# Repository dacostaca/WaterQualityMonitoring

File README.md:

# Water Quality Monitoring System 🌊

Un sistema autónomo de monitoreo de calidad del agua basado en ESP32 con cuatro sensores: pH, temperatura, TDS y turbidez. Incluye implementación de Deep Sleep y Watchdog Timer para operación autónoma y monitoreo de errores.

---

## 📋 Tabla de Contenidos

- [Descripción General](#-descripción-general)
- [Estado del Proyecto](#-estado-del-proyecto)
- [Estructura del Repositorio](#-estructura-del-repositorio)
  - [Etapa I - Trabajo Previo](#etapa-i---trabajo-previo)
  - [Etapa II - Desarrollo Actual](#etapa-ii---desarrollo-actual)
  - [Código del Firmware (MonitorAgua_ESP32)](#código-del-firmware-monitoragua_esp32)
  - [Código del Servidor (monitor_agua_pagina)](#código-del-servidor-monitor_agua_pagina)
- [Documentación del Código](#-documentación-del-código)
- [Inicio Rápido](#-inicio-rápido)
- [Requisitos](#-requisitos)
- [Colaboradores](#-colaboradores)
- [Licencia](#-licencia)

---

## 🌟 Descripción General

Este proyecto implementa un sistema de monitoreo de calidad del agua diseñado para operar de forma autónoma. El sistema mide cuatro parámetros críticos del agua (pH, temperatura, TDS y turbidez) y transmite los datos a un servidor web para su visualización y análisis.

### ¿Qué mide el sistema?

- **pH**: Nivel de acidez/alcalinidad del agua (0-14)
- **Temperatura**: Temperatura del agua en °C usando sensor DS18B20
- **TDS (Total Dissolved Solids)**: Concentración de sólidos disueltos en ppm
- **Turbidez**: Claridad del agua en NTU

### Aplicaciones

- Monitoreo ambiental de cuerpos de agua naturales
- Control de calidad en plantas de tratamiento
- Investigación científica y educativa
- Acuicultura y piscicultura
- Sistemas de agua potable

---

## 📌 Estado del Proyecto

**Estado actual**: El desarrollo del proyecto ha sido completado en su Etapa II. El sistema se encuentra funcional y documentado, listo para su uso o para ser retomado por futuros desarrolladores que deseen realizar mejoras o extensiones.

**Última actualización**: 09 de diciembre de 2025 (Etapa II)

---

## 📁 Estructura del Repositorio

```
WaterQualityMonitoring/
│
├── Etapa I/                        # Trabajo previo del proyecto (01-08-2025)
│   ├── diseños_pcb/               # Diseños de PCB originales
│   └── documentacion.pdf          # Documentación de la etapa inicial
│
<<<<<<< HEAD
├── Etapa II/                       # Desarrollo actual (09-12-2025)
=======
├── Etapa II/                       # Desarrollo más reciente 
>>>>>>> 25c87ceb19cd74b694c54b1f2cf4447b98eb3ab7
│   ├── Manual de Usuario.md       # Guía completa para el usuario
│   ├── Pruebas y Validación.pdf   # Documento de pruebas realizadas
│   └── registro sistema de monitoreo.rar  # Fotos y fuente LaTeX
│
├── MonitorAgua_ESP32/             # Código del firmware (ESP32)
│   ├── .vscode/                   # Configuración de Visual Studio Code
│   ├── include/                   # Archivos de cabecera (placeholder)
│   ├── lib/                       # Librerías del proyecto
│   ├── src/                       # Código fuente principal
│   ├── test/                      # Directorio de tests (placeholder)
│   ├── .gitignore                # Archivos ignorados por Git
│   ├── Doxyfile                  # Configuración para Doxygen
│   └── platformio.ini            # Configuración de PlatformIO
│
├── monitor_agua_pagina/           # Código del servidor web
│   ├── web_interface/            # Interfaz web del sistema
│   └── servidor.py               # Servidor Python
│
└── README.md                     # Este archivo
```

---

## 📂 Descripción de Carpetas

### Etapa I - Trabajo Previo

**Fecha de entrega**: 01 de agosto de 2025

La carpeta **`Etapa I/`** contiene el trabajo realizado por los desarrolladores iniciales del proyecto:

#### 📐 Diseños de PCB
- **Ubicación**: `Etapa I/diseños_pcb/`
- **Contenido**: Archivos de diseño de la placa de circuito impreso (PCB) utilizados en las versiones iniciales del proyecto
- **Propósito**: Referencia para entender el hardware original y base para mejoras futuras

#### 📄 Documentación Inicial
- **Ubicación**: `Etapa I/documentacion.pdf`
- **Contenido**: Documentación técnica del proyecto en su fase inicial
- **Incluye**: 
  - Especificaciones originales del sistema
  - Diagramas de conexión
  - Resultados de pruebas preliminares
  - Decisiones de diseño tomadas

**Colaboradores Etapa I:**
- Maria Alejandra González Duque
- Juan Carlos Delgado Figueroa

---

### Etapa II - Desarrollo Actual

**Fecha de entrega**: 09 de diciembre de 2025

La carpeta **`Etapa II/`** contiene el trabajo realizado durante el segundo semestre de 2025:

#### 📖 Manual de Usuario
- **Archivo**: `Etapa II/Manual de Usuario.md`
- **Descripción**: Guía completa y detallada para usuarios finales del sistema
- **Contenido**:
  - Instalación del entorno de desarrollo (Visual Studio Code y PlatformIO)
  - Configuración del hardware y drivers
  - Conexión física de sensores a los pines GPIO
  - Flasheo del programa a la ESP32
  - Configuración de red WiFi
  - Uso del sistema y visualización de datos
  - Solución de problemas comunes
  - Referencias y recursos adicionales
- **Audiencia**: Usuarios finales, técnicos, estudiantes

#### 🧪 Documento de Pruebas y Validación
- **Archivo**: `Etapa II/Pruebas y Validación.pdf`
- **Descripción**: Documentación de todas las pruebas realizadas al sistema
- **Contenido**:
  - Metodología de pruebas
  - Casos de prueba ejecutados
  - Resultados obtenidos
  - Análisis de desempeño del sistema
  - Validación de funcionalidades
  - Conclusiones y recomendaciones
- **Propósito**: Validar el correcto funcionamiento del sistema y documentar su rendimiento

#### 📸 Registro del Sistema (LaTeX)
- **Archivo**: `Etapa II/registro sistema de monitoreo.rar`
- **Contenido**:
  - **Fotografías**: Imágenes del sistema ensamblado, sensores conectados, pruebas en campo
  - **Fuente LaTeX**: Archivos `.tex` del documento de registro
  - **Recursos**: Figuras, tablas y archivos auxiliares para compilar el documento
- **Propósito**: Documentación visual del proyecto y fuente editable para reportes académicos
- **Uso**: Descomprimir el archivo RAR y compilar el documento LaTeX para visualizar el registro completo del sistema

**Colaboradores Etapa II:**
- Daniel Felipe Acosta Castro
- Oscar Santiago Erazo Mora

*Estudiantes de Ingeniería Electrónica, Universidad Nacional de Colombia*

---

### Código del Firmware (MonitorAgua_ESP32)

La carpeta **`MonitorAgua_ESP32/`** contiene todo el código que se ejecuta en la placa ESP32.

#### Estructura del Firmware

```
MonitorAgua_ESP32/
│
├── .vscode/                       # Configuración del entorno VSCode
│   └── [archivos de configuración]
│
├── include/                       # Directorio para archivos de cabecera
│   └── README                    # Archivo placeholder
│
├── lib/                          # Librerías personalizadas del proyecto
│   ├── CalibrationManager/      # Gestión de calibración de sensores
│   │   ├── CalibrationManager.cpp
│   │   └── CalibrationManager.h
│   │
│   ├── DeepSleep/               # Implementación de modo Deep Sleep
│   │   ├── DeepSleep.cpp
│   │   └── DeepSleep.h
│   │
│   ├── RTC/                     # Control del reloj de tiempo real (RTC)
│   │   ├── RTC.cpp
│   │   └── RTC.h
│   │
│   ├── RTCMemory/               # Gestión de memoria del RTC
│   │   ├── RTCMemory.cpp
│   │   └── RTCMemory.h
│   │
│   ├── Sensors/                 # Controladores de sensores
│   │   ├── pH.cpp              # Sensor de pH
│   │   ├── pH.h
│   │   ├── Temperature.cpp     # Sensor de temperatura DS18B20
│   │   ├── Temperature.h
│   │   ├── TDS.cpp             # Sensor TDS
│   │   ├── TDS.h
│   │   ├── Turbidity.cpp       # Sensor de turbidez
│   │   └── Turbidity.h
│   │
│   ├── WatchDog/                # Implementación del Watchdog Timer
│   │   ├── WatchDog.cpp
│   │   └── WatchDog.h
│   │
│   └── WifiManager/             # Gestión de conectividad WiFi
│       ├── WifiManager.cpp
│       └── WifiManager.h
│
├── src/                          # Código fuente principal
│   └── main.cpp                 # Punto de entrada del programa
│
├── test/                         # Directorio para tests unitarios
│   └── README                   # Archivo placeholder
│
├── .gitignore                    # Archivos ignorados por Git
├── Doxyfile                      # Configuración de Doxygen
└── platformio.ini                # Configuración de PlatformIO
```

#### Descripción de Componentes del Firmware

##### Librerías Principales

- **CalibrationManager**: Gestiona los valores de calibración de los sensores, permitiendo ajustar las lecturas para mayor precisión
- **DeepSleep**: Implementa el modo de bajo consumo de energía, haciendo que la ESP32 entre en Deep Sleep entre mediciones para optimizar el uso de batería
- **RTC**: Maneja la comunicación con el módulo de reloj de tiempo real (RTC DS3231) para mantener estampas de tiempo precisas
- **RTCMemory**: Gestiona el almacenamiento de datos en la memoria del RTC que persiste durante los ciclos de Deep Sleep
- **Sensors**: Contiene los controladores para cada uno de los cuatro sensores:
  - **pH**: Sensor analógico de pH que mide acidez/alcalinidad del agua
  - **Temperature**: Sensor digital DS18B20 que usa protocolo OneWire
  - **TDS**: Sensor analógico de sólidos totales disueltos
  - **Turbidity**: Sensor analógico de turbidez que mide claridad del agua
- **WatchDog**: Implementa el temporizador Watchdog para reiniciar automáticamente el sistema en caso de fallos o bloqueos
- **WifiManager**: Gestiona la conexión WiFi, reconexión automática y comunicación con el servidor

##### Código Principal

- **main.cpp**: Programa principal que orquesta todas las funcionalidades:
  - Inicialización de sensores y periféricos
  - Bucle principal de medición
  - Almacenamiento local de datos
  - Gestión de ciclos de Deep Sleep
  - Conexión periódica a WiFi para transmisión de datos

#### Archivos de Configuración

- **platformio.ini**: Define la configuración del proyecto para PlatformIO, incluyendo:
  - Placa objetivo (ESP32)
  - Framework (Arduino)
  - Librerías externas requeridas
  - Velocidad de baudios para comunicación serial
  - Flags de compilación

- **Doxyfile**: Configuración para generar documentación automática del código usando Doxygen

#### Funcionalidades Principales del Firmware

- ⚡ **Adquisición de datos**: Lee valores de los cuatro sensores de forma periódica
- 💾 **Almacenamiento local**: Guarda mediciones en memoria del RTC cuando no hay conectividad
- 🌐 **Conectividad WiFi**: Se conecta a red configurada para transmisión de datos al servidor
- ⏰ **RTC externo**: Mantiene estampas de tiempo precisas con batería de respaldo
- 🔋 **Deep Sleep**: Reduce consumo de energía entrando en modo de bajo consumo entre mediciones
- 🛡️ **Watchdog Timer**: Reinicia automáticamente el sistema ante fallos o bloqueos
- 📊 **Calibración**: Sistema de calibración para ajustar lecturas de sensores
- 📡 **Protocolo OneWire**: Comunicación con sensor de temperatura DS18B20

---

### Código del Servidor (monitor_agua_pagina)

La carpeta **`monitor_agua_pagina/`** contiene el servidor web que recibe y visualiza los datos del sistema.

#### Estructura del Servidor

```
monitor_agua_pagina/
│
├── web_interface/                # Interfaz web del sistema
│   ├── css/                     # Hojas de estilo
│   │   └── styles.css          # Estilos de la interfaz
│   │
│   ├── js/                      # JavaScript del cliente
│   │   └── script.js           # Lógica de la interfaz web
│   │
│   └── index.html               # Página principal
│
└── servidor.py                   # Servidor Python
```

#### Descripción de Componentes del Servidor

##### Servidor Backend

- **servidor.py**: Servidor web implementado en Python que maneja:
  - Recepción de datos enviados por la ESP32
  - Procesamiento y validación de mediciones
  - Almacenamiento temporal de datos
  - Servicio de la interfaz web
  - API para consulta de datos históricos

##### Interfaz Web (web_interface/)

- **index.html**: Página principal de la aplicación web que proporciona:
  - Visualización de datos en tiempo real
  - Gráficos de tendencias de mediciones
  - Tabla con historial de datos (últimas 120 mediciones por defecto)
  - Botón para solicitar datos almacenados en la ESP32
  - Indicadores de estado de conexión

- **styles.css**: Hoja de estilos que define:
  - Diseño y apariencia de la interfaz
  - Estilos para gráficos y tablas
  - Diseño responsivo
  - Indicadores visuales de estado

- **script.js**: JavaScript del lado del cliente que maneja:
  - Solicitudes AJAX al servidor
  - Actualización dinámica de la interfaz
  - Generación de gráficos interactivos
  - Procesamiento y visualización de datos recibidos
  - Gestión de eventos de usuario (botones, filtros, etc.)

#### Funcionalidades del Servidor

- 🌐 **API REST**: Endpoints para recibir datos de la ESP32 vía HTTP
- 📊 **Visualización**: Interfaz web para mostrar datos en tiempo real y tendencias
- 💾 **Almacenamiento temporal**: Mantiene datos recientes en memoria para consulta
- 🔄 **Actualización dinámica**: Refresca automáticamente la interfaz con nuevos datos
- 📈 **Gráficos**: Generación de gráficos de series de tiempo para cada sensor
- 🎨 **Interfaz responsiva**: Diseño adaptable a diferentes tamaños de pantalla

#### Tecnologías Utilizadas

- **Backend**: Python (servidor web)
- **Frontend**: HTML5, CSS3, JavaScript
- **Comunicación**: HTTP/REST API
- **Visualización**: JavaScript (librerías de gráficos integradas en script.js)

---

## 📖 Documentación del Código

### Documentación Doxygen del Firmware

El código del firmware en la carpeta **`MonitorAgua_ESP32/`** está completamente documentado utilizando el estándar **Doxygen**. Esto permite generar documentación HTML profesional de forma automática a partir de los comentarios en el código.

#### ¿Qué es Doxygen?

Doxygen es una herramienta que extrae comentarios especialmente formateados del código fuente y genera documentación en varios formatos (HTML, PDF, LaTeX). Es ampliamente utilizado en proyectos de software para mantener la documentación sincronizada con el código.

#### 📚 Generación de la Documentación

##### Prerrequisitos

Antes de generar la documentación, asegúrese de tener Doxygen instalado:

**Windows:**
1. Descargue el instalador desde: https://www.doxygen.nl/download.html
2. Ejecute el instalador y siga las instrucciones

##### Pasos para Generar la Documentación

1. **Abrir una terminal** (Command Prompt o PowerShell) en la carpeta raíz del firmware:
   ```
   cd MonitorAgua_ESP32
   ```

2. **Ejecutar el comando de Doxygen**:
   ```
   doxygen Doxyfile
   ```

3. **Esperar** a que el proceso termine. Verá mensajes en la terminal indicando el progreso de la generación.

4. **Acceder a la documentación generada**:
   - Una vez completado el proceso, se creará una carpeta llamada **`html/`** dentro del proyecto `MonitorAgua_ESP32/`
   - Navegue a la carpeta: `MonitorAgua_ESP32/html/`
   - Abra el archivo **`index.html`** en su navegador web preferido (doble clic sobre el archivo)

##### Contenido de la Documentación

La documentación generada incluye:

- **Índice de archivos**: Listado de todos los archivos del proyecto con su descripción
- **Índice de clases**: Todas las clases definidas con sus métodos y atributos
- **Índice de funciones**: Listado alfabético de todas las funciones del proyecto
- **Diagramas de clases**: Visualización de relaciones entre clases (requiere Graphviz)
- **Diagramas de dependencias**: Muestra qué archivos dependen de otros
- **Gráficos de llamadas**: Ilustra qué funciones llaman a otras funciones
- **Documentación detallada**: Descripción completa de cada función con:
  - Propósito y funcionalidad
  - Parámetros de entrada
  - Valores de retorno
  - Notas y advertencias
  - Ejemplos de uso (cuando aplica)

##### Navegación de la Documentación

Una vez abierto `index.html`:

1. Use el menú superior para navegar entre secciones:
   - **Files**: Ver todos los archivos del proyecto
   - **Classes**: Ver las clases definidas
   - **Functions**: Buscar funciones específicas

2. Use la barra de búsqueda en la esquina superior derecha para encontrar elementos específicos

3. Haga clic en cualquier elemento para ver su documentación detallada

---

## 🚀 Inicio Rápido

### 1. Clonar el Repositorio

```bash
git clone https://github.com/dacostaca/WaterQualityMonitoring.git
cd WaterQualityMonitoring
```

### 2. Configurar el Firmware (ESP32)

1. Abra Visual Studio Code
2. Instale la extensión PlatformIO IDE
3. Abra la carpeta `MonitorAgua_ESP32` con PlatformIO
4. Conecte la ESP32 al computador mediante USB
5. Compile y flashee el programa usando el botón "Upload" (→) en la barra inferior de PlatformIO

**Nota importante**: El puerto USB Tipo C de la ESP32 solo funciona en **una orientación**. Si el computador no detecta la placa, desconecte el cable USB, voltéelo e intente conectar nuevamente.

### 3. Configurar el Servidor

1. Navegue a la carpeta del servidor:
   ```bash
   cd monitor_agua_pagina
   ```

2. Asegúrese de tener Python instalado en su sistema

3. Ejecute el servidor:
   ```bash
   python servidor.py
   ```

### 4. Acceder a la Interfaz Web

1. Abra su navegador web
2. Vaya a la dirección proporcionada por el servidor (típicamente `http://localhost:5000` o similar)
3. Espere a que la ESP32 se conecte a la red WiFi configurada
4. Use el botón "Solicitar Datos" para descargar las mediciones almacenadas en la ESP32

### 5. Configurar Red WiFi

El sistema está configurado por defecto para conectarse a:
- **SSID**: `RED_MONITOREO`
- **Contraseña**: `Holamundo6`

Para cambiar estas credenciales, edite el archivo de configuración en el firmware y vuelva a flashear el programa.

---

## 🔧 Requisitos

### Hardware

- **Placa**: ESP32 S2 o compatible
- **Sensores DFRobot**:
  - Sensor de pH (analógico)
  - Sensor de temperatura DS18B20 (digital, protocolo OneWire)
  - Sensor TDS (analógico)
  - Sensor de turbidez (analógico)
- **Módulo RTC**: DS3231 con batería CR2032 de 3.3V
- **Cable**: USB Tipo C
- **Alimentación**: 5V (USB o fuente externa)
- **Computador**: Windows 10/11 con puerto USB disponible

### Software

- **[Visual Studio Code](https://code.visualstudio.com/)** - Editor de código
- **[PlatformIO IDE](https://platformio.org/)** - Extensión para VSCode
- **[Python](https://www.python.org/downloads/)** - Para ejecutar el servidor (versión 3.7 o superior)
- **[CP210x USB to UART Bridge Drivers](https://www.silabs.com/developers/usb-to-uart-bridge-vcp-drivers)** - Drivers para comunicación con ESP32
- **[Doxygen](https://www.doxygen.nl/download.html)** - (Opcional) Para generar documentación del código
- **[Graphviz](https://graphviz.org/download/)** - (Opcional) Para diagramas en Doxygen

### Conocimientos Recomendados

- Manejo básico de Visual Studio Code
- Conceptos básicos de electrónica (voltaje, corriente, conexión de sensores)
- Navegación en interfaces web
- Conocimientos básicos de línea de comandos (para ejecutar el servidor)

---

## 📄 Documentación Adicional

Para información detallada sobre el uso del sistema, consulte:

- **[Manual de Usuario](Etapa%20II/Manual%20de%20Usuario.md)**: Guía completa de instalación, configuración y uso
- **[Pruebas y Validación](Etapa%20II/Pruebas%20y%20Validación.pdf)**: Resultados de las pruebas realizadas al sistema
- **[Registro LaTeX](Etapa%20II/registro%20sistema%20de%20monitoreo.rar)**: Documentación visual y fuente LaTeX (descomprimir para acceder)
- **[Documentación Etapa I](Etapa%20I/documentacion.pdf)**: Trabajo previo del proyecto
- **Documentación del código**: Generar con Doxygen siguiendo las instrucciones de la sección anterior

---

## 👥 Colaboradores

### Etapa I (01 de agosto de 2025)
- **Maria Alejandra González Duque**
- **Juan Carlos Delgado Figueroa**

*Responsables del diseño inicial de hardware y primera implementación del sistema*

### Etapa II (09 de diciembre de 2025)
- **Daniel Felipe Acosta Castro** - [GitHub](https://github.com/dacostaca)
- **Oscar Santiago Erazo Mora**

*Estudiantes de Ingeniería Electrónica*  
*Universidad Nacional de Colombia*  
*Segundo semestre de 2025*

---

## 🙏 Agradecimientos

- DFRobot por la documentación de los sensores utilizados
- Comunidad de PlatformIO por las herramientas de desarrollo
- Espressif por el soporte de ESP32
- Universidad Nacional de Colombia por el apoyo académico

---

**⭐ Si este proyecto te fue útil, considera darle una estrella en GitHub ⭐**

---

<<<<<<< HEAD
*Proyecto desarrollado como parte del programa de Ingeniería Electrónica*  
*Universidad Nacional de Colombia - 2025*
=======
*Última actualización: Diciembre 2024*
>>>>>>> 25c87ceb19cd74b694c54b1f2cf4447b98eb3ab7

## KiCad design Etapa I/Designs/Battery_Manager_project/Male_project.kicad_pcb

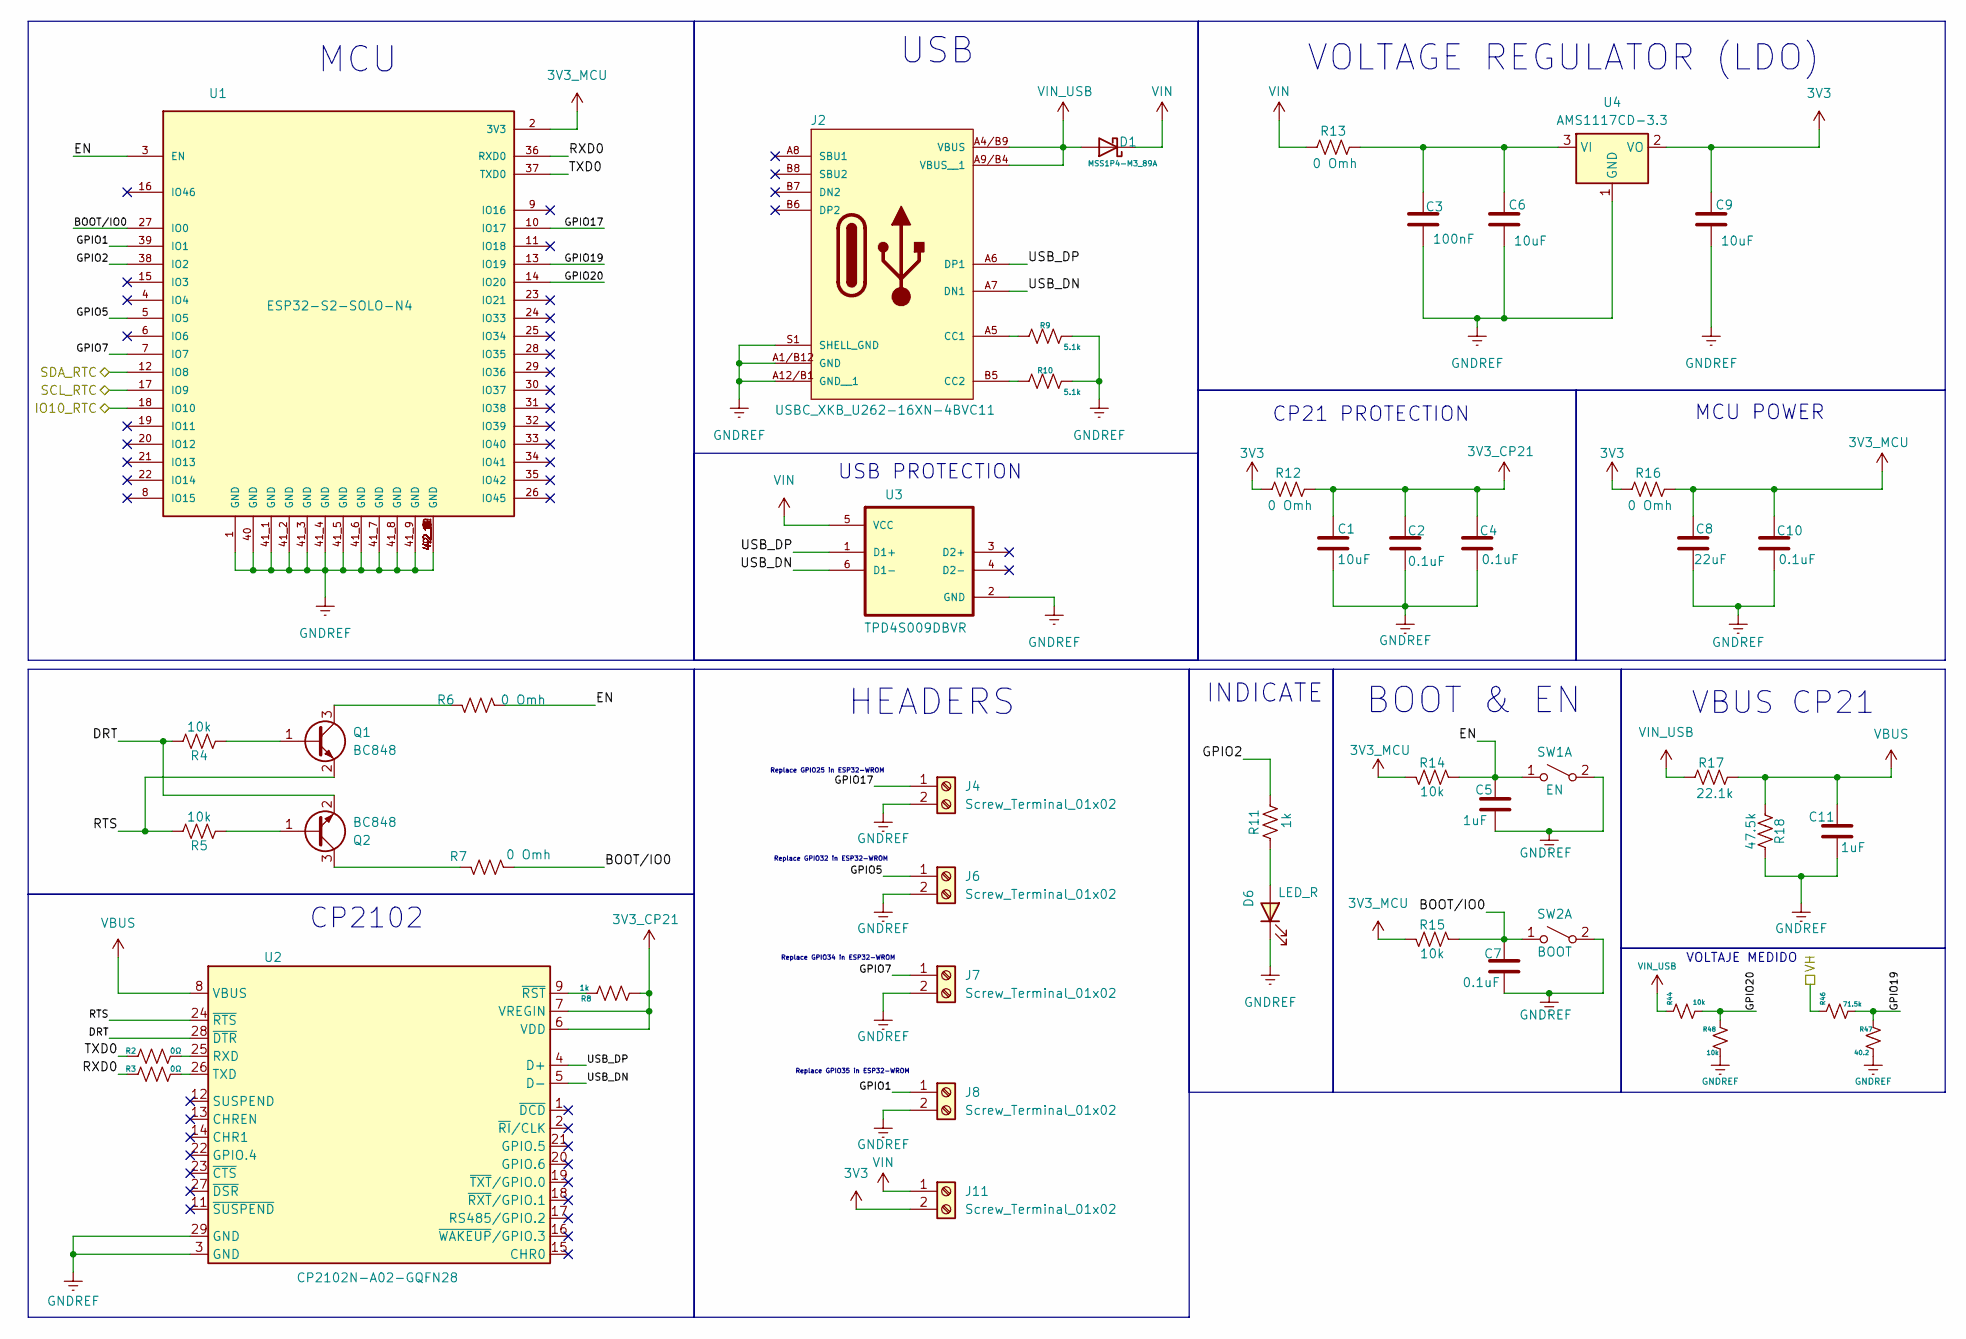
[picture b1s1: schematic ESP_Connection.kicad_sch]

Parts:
C1, C6, C9: 10uF; C_0805_2012Metric
C2, C4, C7, C10: 0.1uF; C_1206_3216Metric
C3: 100nF; C_0603_1608Metric; Mnf. Part # CC0603KRX7R7BB104
C5, C11: 1uF; C_0805_2012Metric; Manufacturer # CC0805KKX7R7BB105
C8: 22uF; C_0805_2012Metric
D1: MSS1P4-M3_89A; DIODE_MSS1P4-M3_89A
D6: LED_R; D_0603_1608Metric; Manufacturer # TLMS1100-GS08
J2: USBC_XKB_U262-16XN-4BVC11; USBC_Receptacle_XKB_U262-16XN-4BVC11; PARTREV B4
J4, J6, J7, J8, J11: Screw_Terminal_01x02; TerminalBlock_MaiXu_MX126-5.0-02P_1x02_P5.00mm
Q1, Q2: BC848; SOT-23
R2, R3: 0Ω; R_0603_1608Metric
R4, R5, R14, R15: 10k; R_0603_1608Metric; Manufacturer # CR0603-FX-1002ELF
R6, R7, R12, R13, R16: 0 Omh; R_0603_1608Metric
R8, R11: 1k; R_0603_1608Metric
R9, R10: 5.1k; R_1206_3216Metric
R17: 22.1k; R_0402_1005Metric
R18: 47.5k; R_0603_1608Metric; Manufacturer # CR0603-FX-1002ELF
R44, R48: 10k; R_0603_1608Metric
R46: 71.5k; R_0603_1608Metric
R47: 40.2; R_0603_1608Metric
SW1: EN; PTS810SJG250SMTR LFS; Manufacturer # PTS810SJG250SMTR LFS
SW2: BOOT; PTS810SJG250SMTR LFS; Manufacturer # PTS810SJG250SMTR LFS
U1: ESP32-S2-SOLO-N4; XCVR_ESP32-S2-SOLO-N4; PARTREV 1.6
U2: CP2102N-A02-GQFN28; QFN-28-1EP_5x5mm_P0.5mm_EP3.35x3.35mm
U3: TPD4S009DBVR; SOT95P280X145-6N
U4: AMS1117CD-3.3; TO-252-2

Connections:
3V3: C9.1, J11.2, R12.1, R16.1, U4.2 (VO); also elsewhere on the board
3V3_CP21: C1.1, C2.1, C4.1, R8.1, R12.2, U2.6 (VDD), U2.7 (VREGIN)
3V3_MCU: C8.1, C10.1, R14.2, R15.2, R16.2, U1.2 (3V3)
/Battery_Manager/IO10_RTC: U1.18 (IO10); also elsewhere on the board
/Battery_Manager/SCL_RTC: U1.17 (IO9); also elsewhere on the board
/Battery_Manager/SDA_RTC: U1.12 (IO8); also elsewhere on the board
/Battery_Manager/VH: R46.1; also elsewhere on the board
/MCU/BOOT/IO0: C7.1, R7.1, R15.1, SW2.1 (B), U1.27 (IO0)
/MCU/DRT: Q2.2 (E), R4.2, U2.28 (~DTR)
/MCU/EN: C5.1, R6.1, R14.1, SW1.1 (B), U1.3 (EN)
/MCU/GPIO1: J8.1, U1.39 (IO1)
/MCU/GPIO2: R11.2, U1.38 (IO2)
/MCU/GPIO5: J6.1, U1.5 (IO5)
/MCU/GPIO7: J7.1, U1.7 (IO7)
/MCU/GPIO17: J4.1, U1.10 (IO17)
/MCU/GPIO19: R46.2, R47.1, U1.13 (IO19)
/MCU/GPIO20: R44.2, R48.1, U1.14 (IO20)
/MCU/RTS: Q1.2 (E), R5.2, U2.24 (~RTS)
/MCU/RXD0: R3.1, U1.36 (RXD0)
/MCU/TXD0: R2.1, U1.37 (TXD0)
/MCU/USB_DN: J2.A7 (DN1), U2.5 (D-), U3.6 (D1-)
/MCU/USB_DP: J2.A6 (DP1), U2.4 (D+), U3.1 (D1+)
GNDREF: C1.2, C2.2, C3.2, C4.2, C5.2, C6.2, C7.2, C8.2, C9.2, C10.2, C11.2, D6.1 (K), J2.A1/B12 (GND), J2.A12/B1 (GND__1), J2.S1 (SHELL_GND), J4.2, J6.2, J7.2, J8.2, R9.2, R10.2, R18.2, R47.2, R48.2, SW1.2 (A), SW2.2 (A), U1.1 (GND), U1.40 (GND), U1.41_1 (GND), U1.41_2 (GND), U1.41_3 (GND), U1.41_4 (GND), U1.41_5 (GND), U1.41_6 (GND), U1.41_7 (GND), U1.41_8 (GND), U1.41_9 (GND), U1.42_1 (GND), U1.42_2 (GND), U1.42_3 (GND), U1.42_4 (GND), U1.42_5 (GND), U1.42_6 (GND), U1.42_7 (GND), U1.42_8 (GND), U1.42_9 (GND), U1.42_10 (GND), U1.42_11 (GND), U1.42_12 (GND), U2.3 (GND), U2.29 (GND), U3.2 (GND), U4.1 (GND); also elsewhere on the board
unnamed: D6.2 (A), R11.1
unnamed: J2.A5 (CC1), R9.1
unnamed: J2.B5 (CC2), R10.1
unnamed: Q1.1 (B), R4.1
unnamed: Q1.3 (C), R6.2
unnamed: Q2.1 (B), R5.1
unnamed: Q2.3 (C), R7.2
unnamed: R2.2, U2.25 (RXD)
unnamed: R3.2, U2.26 (TXD)
unnamed: R8.2, U2.9 (~RST)
unnamed: C3.1, C6.1, R13.2, U4.3 (VI)
VBUS: C11.1, R17.2, R18.1, U2.8 (VBUS)
VIN: D1.1 (K), J11.1, R13.1, U3.5 (VCC); also elsewhere on the board
VIN_USB: D1.2 (A), J2.A4/B9 (VBUS), J2.A9/B4 (VBUS__1), R17.1, R44.1; also elsewhere on the board

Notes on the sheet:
Replace GPIO35 in ESP32-WROM
USB
VOLTAJE MEDIDO
HEADERS
VBUS CP21
INDICATE
MCU
Replace GPIO34 in ESP32-WROM
Replace GPIO25 in ESP32-WROM
USB PROTECTION
Replace GPIO32 in ESP32-WROM
MCU POWER
CP21 PROTECTION
BOOT & EN
VOLTAGE REGULATOR (LDO)
CP2102

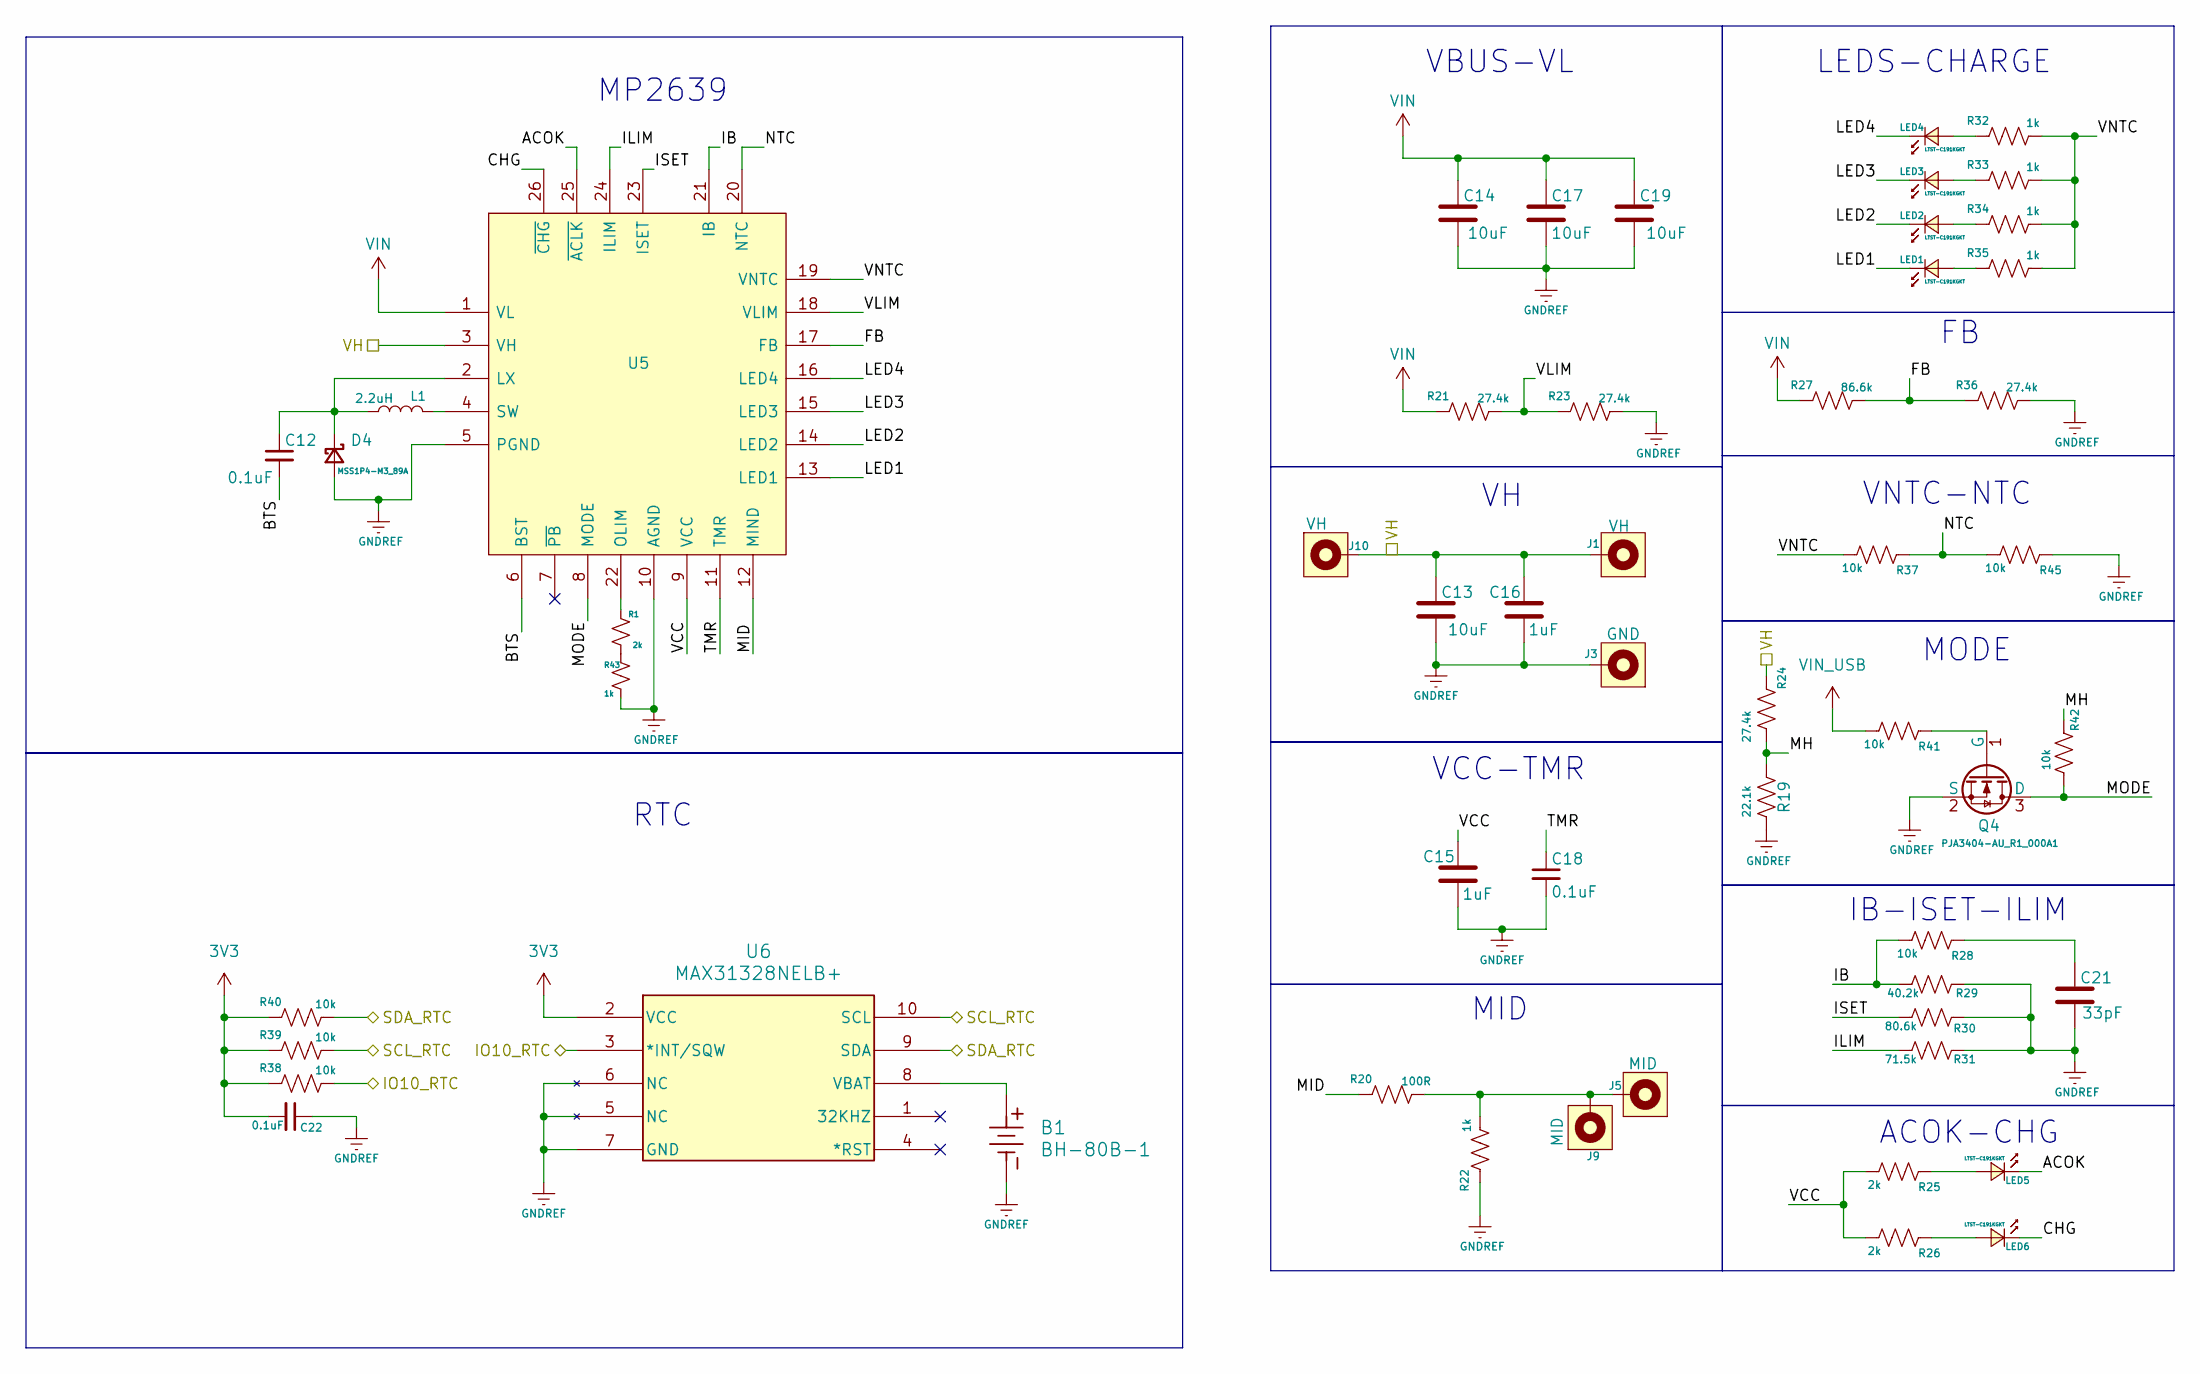
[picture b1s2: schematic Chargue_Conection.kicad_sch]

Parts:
B1: BH-80B-1; BH-80B-1_ADM
C12, C18, C22: 0.1uF; C_0603_1608Metric
C13, C14, C17, C19: 10uF; C_0805_2012Metric
C15, C16: 1uF; C_0805_2012Metric; Manufacturer # CC0805KKX7R7BB105
C21: 33pF; C_0402_1005Metric
D4: MSS1P4-M3_89A; DIODE_MSS1P4-M3_89A
J1, J10: VH; TEST-PIN
J3: GND; TEST-PIN
J5, J9: MID; TEST-PIN
L1: 2.2uH; 0630CDMCCDS-2R2MC___Inductor
LED1, LED2, LED3, LED4, LED5, LED6: LTST-C191KGKT; LED_0603_1608Metric
Q4: PJA3404-AU_R1_000A1; SOT-23
R1, R25, R26: 2k; R_0603_1608Metric
R19: 22.1k; R_0402_1005Metric
R20: 100R; R_0603_1608Metric
R21, R23, R24: 27.4k; C_0603_1608Metric; Man. part# RC0603FR-0727K4L
R22, R32, R33, R34, R35, R43: 1k; R_0603_1608Metric
R27: 86.6k; R_0603_1608Metric
R28, R37, R38, R39, R40, R41, R42, R45: 10k; R_0603_1608Metric
R29: 40.2k; R_0603_1608Metric
R30: 80.6k; R_0603_1608Metric
R31: 71.5k; R_0603_1608Metric
R36: 27.4k; R_0603_1608Metric
U5: MP2639AGR-Z; MP2639AGRZ; Mouser Part Number 946-MP2639AGR-Z
U6: MAX31328NELB+; 21-0140AK_L1055M-1_MXM

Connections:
3V3: C22.2, R38.1, R39.1, R40.1, U6.2 (VCC); also elsewhere on the board
/Battery_Manager/ACOK: LED5.1 (K), U5.25 (~ACLK)
/Battery_Manager/BTS: C12.2, U5.6 (BST)
/Battery_Manager/CHG: LED6.1 (K), U5.26 (~CHG)
/Battery_Manager/FB: R27.2, R36.1, U5.17 (FB)
/Battery_Manager/IB: R28.2, R29.2, U5.21 (IB)
/Battery_Manager/ILIM: R31.2, U5.24 (ILIM)
/Battery_Manager/IO10_RTC: R38.2, U6.3 (*INT/SQW); also elsewhere on the board
/Battery_Manager/ISET: R30.2, U5.23 (ISET)
/Battery_Manager/LED1: LED1.1 (K), U5.13 (LED1)
/Battery_Manager/LED2: LED2.1 (K), U5.14 (LED2)
/Battery_Manager/LED3: LED3.1 (K), U5.15 (LED3)
/Battery_Manager/LED4: LED4.1 (K), U5.16 (LED4)
/Battery_Manager/MH: R19.1, R24.2, R42.1
/Battery_Manager/MID: R20.1, U5.12 (MIND)
/Battery_Manager/MODE: Q4.3 (D), R42.2, U5.8 (MODE)
/Battery_Manager/NTC: R37.1, R45.2, U5.20 (NTC)
/Battery_Manager/SCL_RTC: R39.2, U6.10 (SCL); also elsewhere on the board
/Battery_Manager/SDA_RTC: R40.2, U6.9 (SDA); also elsewhere on the board
/Battery_Manager/TMR: C18.1, U5.11 (TMR)
/Battery_Manager/VCC: C15.1, R25.2, R26.2, U5.9 (VCC)
/Battery_Manager/VH: C13.1, C16.1, J1.1, J10.1, R24.1, U5.3 (VH); also elsewhere on the board
/Battery_Manager/VLIM: R21.2, R23.1, U5.18 (VLIM)
/Battery_Manager/VNTC: R32.2, R33.2, R34.2, R35.2, R37.2, U5.19 (VNTC)
GNDREF: B1.1, C13.2, C14.2, C15.2, C16.2, C17.2, C18.2, C19.2, C21.2, C22.1, D4.2 (A), J3.1, Q4.2 (S), R19.2, R22.1, R23.2, R29.1, R30.1, R31.1, R36.2, R43.2, R45.1, U5.5 (PGND), U5.10 (AGND), U6.5 (NC), U6.6 (NC), U6.7 (GND); also elsewhere on the board
unnamed: C21.1, R28.1
unnamed: C12.1, D4.1 (K), L1.1, U5.2 (LX)
unnamed: J5.1, J9.1, R20.2, R22.2
unnamed: LED1.2 (A), R35.1
unnamed: LED2.2 (A), R34.1
unnamed: LED3.2 (A), R33.1
unnamed: LED4.2 (A), R32.1
unnamed: LED5.2 (A), R25.1
unnamed: LED6.2 (A), R26.1
unnamed: Q4.1 (G), R41.1
unnamed: R1.2, R43.1
unnamed: R1.1, U5.22 (OLIM)
unnamed: L1.2, U5.4 (SW)
unnamed: B1.2, U6.8 (VBAT)
VIN: C14.1, C17.1, C19.1, R21.1, R27.1, U5.1 (VL); also elsewhere on the board
VIN_USB: R41.2; also elsewhere on the board

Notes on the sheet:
IB-ISET-ILIM
RTC
VNTC-NTC
VCC-TMR
MODE
ACOK-CHG
MP2639
VBUS-VL
MID
LEDS-CHARGE

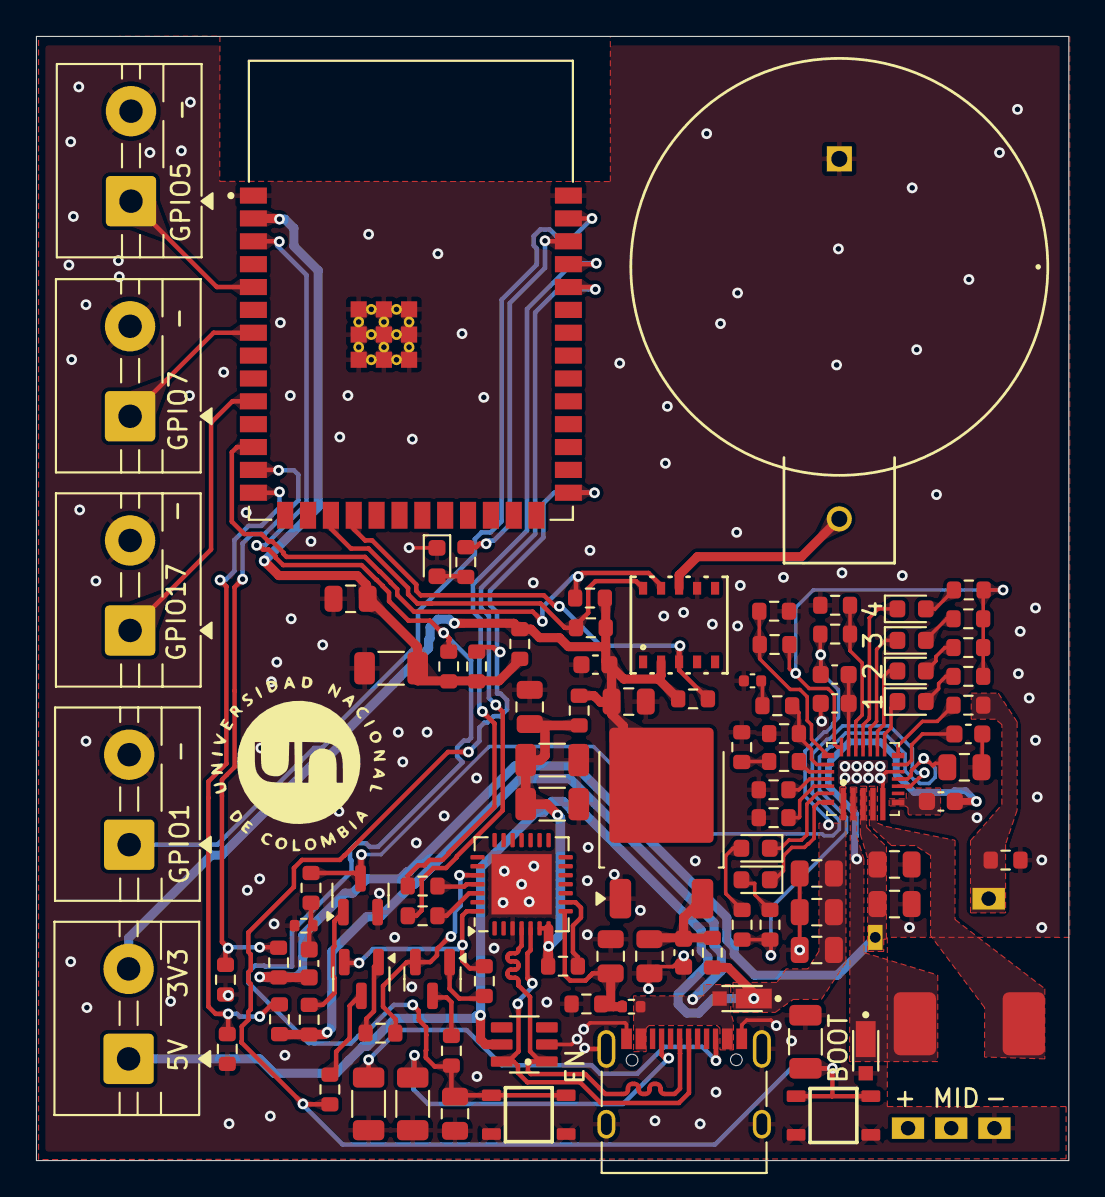
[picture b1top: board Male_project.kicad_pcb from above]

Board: 2 copper layers, 57.4 x 62.5 mm, 102 parts (0 on the bottom side), 70 nets.

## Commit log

2025-08-05 Archivos finales del proyecto sin modificacion
2025-09-26 Comentarios en las librerias de sensores, watchdog y wifi
2025-09-26 Comentarios sensores de Turbidez y Temperatura
2025-11-05 Modificaciónes realizadas: Documentación compatible con Doxygen y variables ajustables de tiempo para la toma de muestras
2025-11-05 Creada nueva rama para gestionar código
2025-11-18 cambios de identación
2025-11-18 Versión combinada con comentarios y arreglos del RTC
2025-11-18 añadiendo carpetas correspondientes al diseño e implementación de websocket para cominucación con pagina web y carpeta de esquematicos de la placa prototipo
2025-12-03 Organización de carpetas por etapa en la que se desarrollaron los documentos
2025-12-07 Agregando documento Doxyfile para generación de documentación en doxygen y probando modificación de gitignore
2025-12-07 Actualización de documentación de Etapas I y II, y actualización de gitignore
2025-12-08 Agregando comentarios para sección CalibrationManager
2025-12-08 Actualización de README del repositorio
2025-12-09 Actualización versión final del arhivo README

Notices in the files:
README.md:
License: MIT
